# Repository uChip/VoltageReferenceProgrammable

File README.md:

Programmable Voltage Reference  
==============================

This repository contains the design files and write-up for a Programmable Voltage Reference.  The reference has a range of 1 mV to 4.095 volts in 1 mV steps.  The accuracy is plus or minus 100 uV for any set value.  The reference value is displayed on a 4 digit LED display and can be set manually using the rotary encoder or remotely over serial (FTDI port).

The software folder contains an Arduino sketch that is source code for the voltage reference firmware.

See the file PVR.pdf for a more detailed explanation of the project design. 

If there is sufficient interest I will build and calibrate a batch of these to sell.  If you would like one, please contact me. 

## Order PCBs  

You can order this PCB directly from OSH Park.  Click on the following link.  
  * Programmable Voltage Reference - https://oshpark.com/shared_projects/aFUNW4O5 

See the Bill of Materials (BOM) file in the repo Hardware folder for a parts list.  

## Status  
  * Rev-D PCB has been tested to be functional.  

## File Formats  

Hardware design files are in "CadSoft EAGLE PCB Design Software" .brd and .sch formats.  A free version of the software can be downloaded from www.cadsoftusa.com. 

The example code is in Arduino .ino format (text).  A free version of the Arduino software can be downloaded from www.arduino.cc.  

## Distribution License  

License:
<br /><span xmlns:dct="http://purl.org/dc/terms/" property="dct:title">Programmable Voltage Reference</span> by <a xmlns:cc="http://creativecommons.org/ns#" href="https://github.com/uChip/VoltageReferenceProgrammable" property="cc:attributionName" rel="cc:attributionURL">C.Schnarel</a> is licensed under a <a rel="license" href="http://creativecommons.org/licenses/by-sa/4.0/">Creative Commons Attribution-ShareAlike 4.0 International License</a>.

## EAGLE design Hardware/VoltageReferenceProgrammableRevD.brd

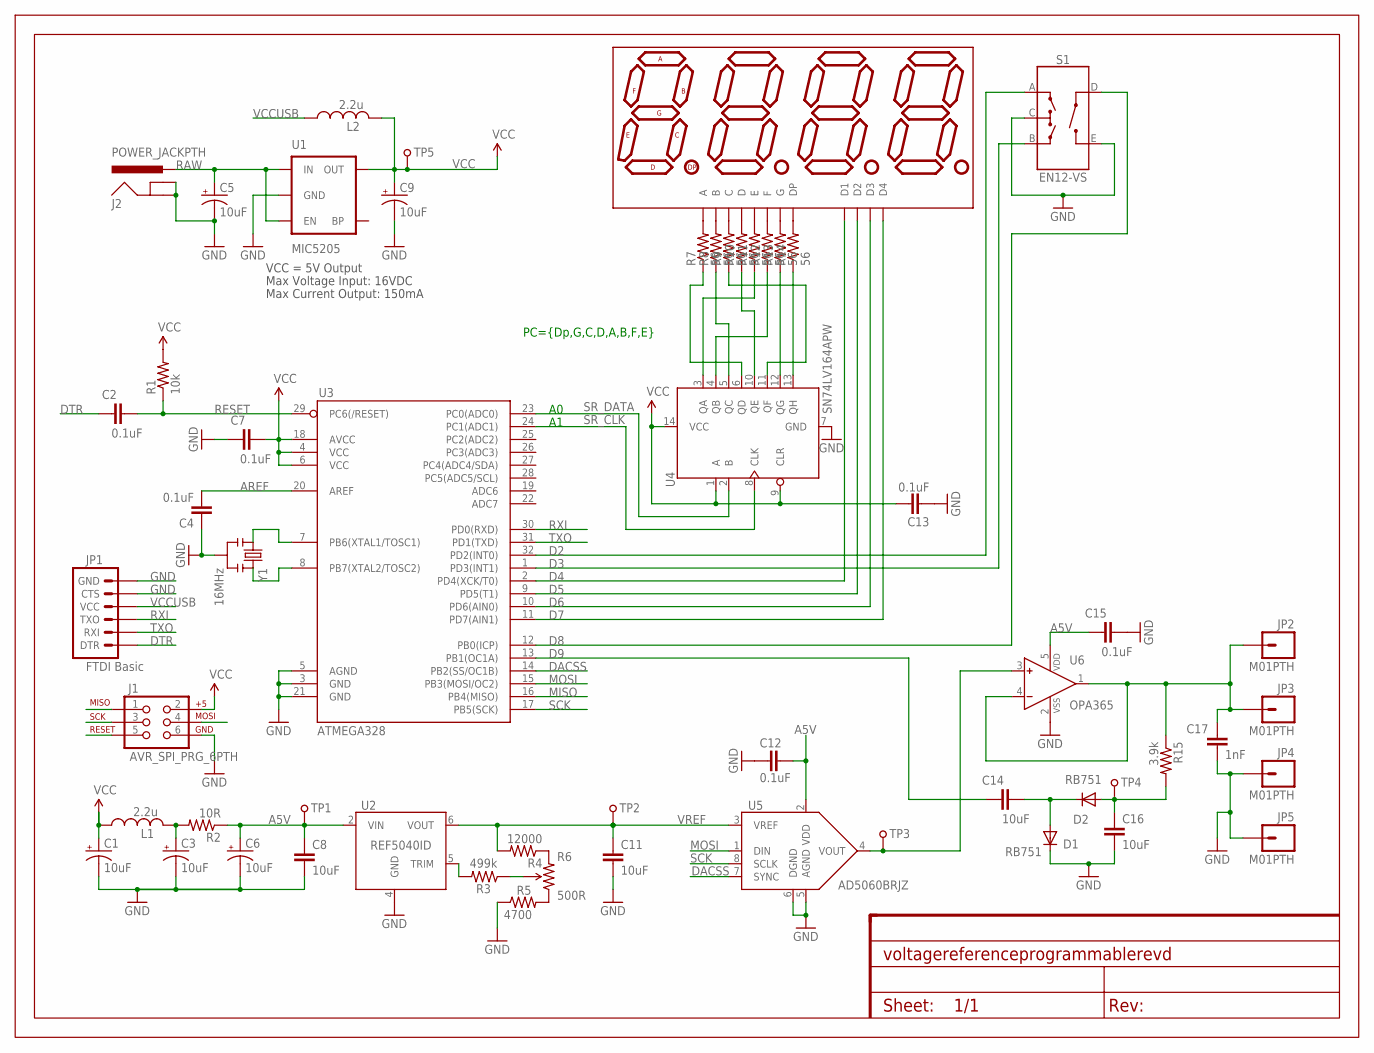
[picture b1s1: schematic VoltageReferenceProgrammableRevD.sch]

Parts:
C1, C3, C5, C6, C9: 10uF; 0805-POL
C2, C4, C7, C12, C13, C15: 0.1uF; 0805
C8, C11, C14, C16: 10uF; 0805
C17: 1nF; 0805
D1, D2: RB751; SOD-323
DISP1: hp; DIL12
FRAME1: FRAME_LTR_CU_MARK; FR-LTR-ON-PCB
J1: AVR_SPI_PRG_6PTH; 2X3
J2: POWER_JACKPTH; POWER_JACK_PTH
JP1: FTDI Basic; 1X06
JP2, JP3, JP4, JP5: M01PTH; 1X01
L1, L2: 2.2u; 0805
R1: 10k; 0805
R2: 10R; 0805
R3: 499k; 0805
R4: 12000; 0805
R5: 4700; 0805
R6: 500R; T93YB
R7, R8, R9, R10, R11, R12, R13, R14: 56; 0805
R15: 3.9k; 0805
S1: EN12-VS; ROTARY_ENCODER_SIDE
TP1, TP2, TP3, TP4, TP5: TEST_POINT; BBD-VIA
U1: MIC5205; SOT23-5
U2: REF5040ID; SOIC-8-MINUSPINS
U3: ATMEGA328; TQFP32-08
U4: SN74LV164APW; TSSOP-14(TI)
U5: AD5060BRJZ; SOT-23-8
U6: OPA365; SOT-23-5
Y1: 16MHz; RESONATOR-SMD

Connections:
A5V: C6.1 (+), C8.1, C12.1, C15.1, R2.1, TP1.P$1, U2.2 (VIN), U5.2 (VDD), U6.5 (VDD)
ADCIN: C16.1, D2.2 (A), R15.2, TP4.P$1
AREF: C4.2, U3.20 (AREF)
D2: S1.A, U3.32 (PD2(INT0))
D3: S1.B, U3.1 (PD3(INT1))
D4: DISP1.1 (D1), U3.2 (PD4(XCK/T0))
D5: DISP1.10 (D2), U3.9 (PD5(T1))
D6: DISP1.4 (D3), U3.10 (PD6(AIN0))
D7: DISP1.6 (D4), U3.11 (PD7(AIN1))
D8: S1.D, U3.12 (PB0(ICP))
D9: C14.1, U3.13 (PB1(OC1A))
DACSS: U3.14 (PB2(SS/OC1B)), U5.7 (SYNC)
DTR: C2.1, JP1.1 (DTR)
GND: C1.2 (-), C3.2 (-), C4.1, C5.2 (-), C6.2 (-), C7.1, C8.2, C9.2 (-), C11.2, C12.2, C13.2, C15.2, C16.2, C17.1, D1.1 (C), J1.6, J2.GND, J2.GNDBREAK, JP1.5 (CTS), JP1.6 (GND), JP4.1, JP5.1, R5.1, S1.C, S1.E, U1.2 (GND), U2.4 (GND), U3.3 (GND), U3.5 (AGND), U3.21 (GND), U4.7 (GND), U5.5 (AGND), U5.6 (DGND), U6.2 (VSS), Y1.2
MISO: J1.1, U3.16 (PB4(MISO))
MOSI: J1.4, U3.15 (PB3(MOSI/OC2)), U5.1 (DIN)
unnamed: U3.7 (PB6(XTAL1/TOSC1)), Y1.1
unnamed: U3.8 (PB7(XTAL2/TOSC2)), Y1.3
unnamed: DISP1.12 (A), R7.2
unnamed: DISP1.11 (B), R8.2
unnamed: DISP1.3 (C), R9.2
unnamed: DISP1.8 (D), R10.2
unnamed: R14.1, U4.13 (QH)
unnamed: DISP1.2 (E), R11.2
unnamed: DISP1.9 (F), R12.2
unnamed: DISP1.7 (G), R13.2
unnamed: DISP1.5 (DP), R14.2
unnamed: TP3.P$1, U5.4 (VOUT), U6.3 (IN+)
unnamed: C17.2, JP2.1, JP3.1, R15.1, U6.1 (OUT), U6.4 (IN-)
unnamed: R3.1, R6.2 (WIPER)
unnamed: R13.1, U4.12 (QG)
unnamed: C14.2, D1.2 (A), D2.1 (C)
unnamed: R3.2, U2.5 (TRIM)
unnamed: R5.2, R6.1 (CCW)
unnamed: R4.1, R6.3 (CW)
unnamed: R9.1, U4.11 (QF)
unnamed: R10.1, U4.10 (QE)
unnamed: R7.1, U4.6 (QD)
unnamed: R8.1, U4.5 (QC)
unnamed: R12.1, U4.4 (QB)
unnamed: R11.1, U4.3 (QA)
unnamed: C3.1 (+), L1.2, R2.2
RAW: C5.1 (+), J2.PWR, U1.1 (IN), U1.3 (EN)
RESET: C2.2, J1.5, R1.1, U3.29 (PC6(/RESET))
RXI: JP1.3 (TXO), U3.30 (PD0(RXD))
SCK: J1.3, U3.17 (PB5(SCK)), U5.8 (SCLK)
SR_CLK: U3.24 (PC1(ADC1)), U4.8 (CLK)
SR_DATA: U3.23 (PC0(ADC0)), U4.2 (B)
TXO: JP1.2 (RXI), U3.31 (PD1(TXD))
VCC: C1.1 (+), C7.2, C9.1 (+), C13.1, J1.2, L1.1, L2.2, R1.2, TP5.P$1, U1.5 (OUT), U3.4 (VCC), U3.6 (VCC), U3.18 (AVCC), U4.1 (A), U4.9 (CLR), U4.14 (VCC)
VCCUSB: JP1.4 (VCC), L2.1
VREF: C11.1, R4.2, TP2.P$1, U2.6 (VOUT), U5.3 (VREF)

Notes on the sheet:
Max Voltage Input: 16VDC
Max Current Output: 150mA
VCC = 5V Output
PC={Dp,G,C,D,A,B,F,E}

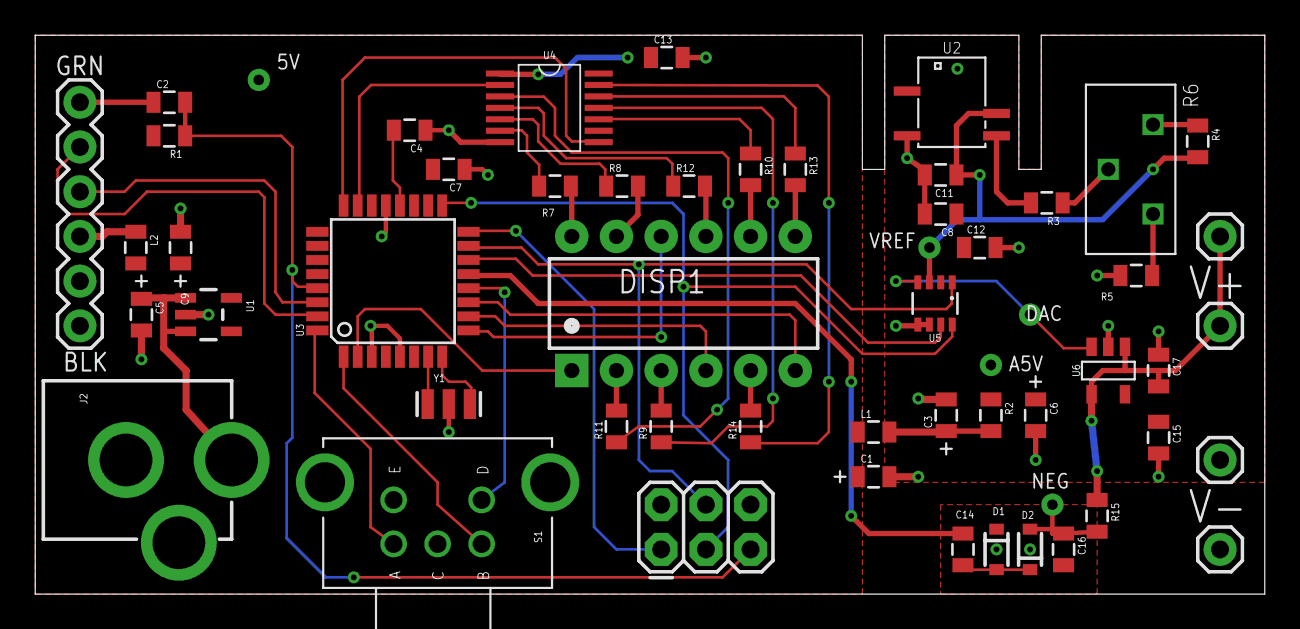
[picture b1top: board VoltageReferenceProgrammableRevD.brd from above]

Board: 2 copper layers, 69.8 x 31.8 mm, 57 parts (0 on the bottom side), 52 nets.

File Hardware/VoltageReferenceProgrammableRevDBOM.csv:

"Qty;""Value"";""Device"";""Package"";""Parts"";""Description"";""CNAME"";""CREVISION"";""DATECODE"";""DESIGNER"";",,,,,,,
"6;""0.1uF"";""CAP0805"";""0805"";""C2", C4, C7, C12, C13," C15"";""Capacitor"";"""";"""";"""";"""";",,
"1;""10R"";""RESISTOR0805-RES"";""0805"";""R2"";""Resistor"";"""";"""";"""";"""";",,,,,,,
"1;""10k"";""RESISTOR0805-RES"";""0805"";""R1"";""Resistor"";"""";"""";"""";"""";",,,,,,,
"4;""10uF"";""CAP0805"";""0805"";""C8", C11, C14," C16"";""Capacitor"";"""";"""";"""";"""";",,,,
"5;""10uF"";""CAP_POL0805"";""0805-POL"";""C1", C3, C5, C6," C9"";"""";"""";"""";"""";"""";",,,
"1;""12000"";""RESISTOR0805-RES"";""0805"";""R4"";""Resistor"";"""";"""";"""";"""";",,,,,,,
"1;""16MHz"";""RESONATORSMD"";""RESONATOR-SMD"";""Y1"";""Resonator"";"""";"""";"""";"""";",,,,,,,
"1;""1nF"";""CAP0805"";""0805"";""C17"";""Capacitor"";"""";"""";"""";"""";",,,,,,,
"2;""2.2u"";""INDUCTOR"";""0805"";""L1"," L2"";""Inductor", SMT chip," 0805 pkg"";"""";"""";"""";"""";",,,,
"1;""3.9k"";""RESISTOR0805-RES"";""0805"";""R15"";""Resistor"";"""";"""";"""";"""";",,,,,,,
"1;""4700"";""RESISTOR0805-RES"";""0805"";""R5"";""Resistor"";"""";"""";"""";"""";",,,,,,,
"1;""499k"";""RESISTOR0805-RES"";""0805"";""R3"";""Resistor"";"""";"""";"""";"""";",,,,,,,
"1;""500R"";""TRIMPOT"";""T93YB"";""R6"";""Various small potentiometers for ""set-and-forget"" applications"";"""";"""";"""";"""";",,,,,,,
"8;""56"";""RESISTOR0805-RES"";""0805"";""R7", R8, R9, R10, R11, R12, R13," R14"";""Resistor"";"""";"""";"""";"""";"
"1;""AD5060BRJZ"";""AD5060BRJZ"";""SOT-23-8"";""U5"";"""";"""";"""";"""";"""";",,,,,,,
"1;""ATMEGA328"";""ATMEGA168"";""TQFP32-08"";""U3"";"""";"""";"""";"""";"""";",,,,,,,
"1;""AVR_SPI_PRG_6PTH"";""AVR_SPI_PRG_6PTH"";""2X3"";""J1"";""AVR ISP 6 Pin"";"""";"""";"""";"""";",,,,,,,
"1;""EN12-VS"";""EN12-VS"";""ROTARY_ENCODER_SIDE"";""S1"";""Rotary Encoder w push switch", quadrature," 12 pulse/rev.  BI Technologies. Digi-key#987-1198-ND"";"""";"""";"""";"""";",,,,,
"1;""FRAME_LTR_CU_MARK"";""FRAME_LTR_CU_MARK"";""FR-LTR-ON-PCB"";""FRAME1"";""This frame is sized for an 8.5x11"" page with a 0.25"" margin.  It also places a name"," datecode and revision mark in the bottom copper layer of the PCB."";""C.Schnarel"";""ProgVRef Rev-D"";""24AUG2014"";""C.Schnarel"";",,,,,,
"1;""FTDI Basic"";""ARDUINO_SERIAL_PROGRAMPTH"";""1X06"";""JP1"";"""";"""";"""";"""";"""";",,,,,,,
"4;""M01PTH"";""M01PTH"";""1X01"";""JP2", JP3, JP4," JP5"";""Header 1"";"""";"""";"""";"""";",,,,
"1;""MIC5205"";""V_REG_LDOSMD"";""SOT23-5"";""U1"";""Voltage Regulator LDO"";"""";"""";"""";"""";",,,,,,,
"1;""OPA365"";""OPA365"";""SOT-23-5"";""U6"";""OpAmp", 50MHz, R-to-R, single-supply, CMOS, TI," Digi-Key#296-20645-1-ND"";"""";"""";"""";"""";",
"1;""POWER_JACKPTH"";""POWER_JACKPTH"";""POWER_JACK_PTH"";""J2"";""Power Jack"";"""";"""";"""";"""";",,,,,,,
"2;""RB751"";""DIODESOD"";""SOD-323"";""D1"," D2"";""Diode"";"""";"""";"""";"""";",,,,,,
"1;""REF5040ID"";""REF5040ID"";""SOIC-8-MINUSPINS"";""U2"";"""";"""";"""";"""";"""";",,,,,,,
"1;""SN74LV164APW"";""SN74LV164APW"";""TSSOP-14(TI)"";""U4"";""8-BIT SERIAL-IN PARALLEL-OUT SHIFT REGISTER with clear"";"""";"""";"""";"""";",,,,,,,
"5;""TEST_POINT"";""TEST_POINT"";""BBD-VIA"";""TP1", TP2, TP3, TP4," TP5"";""Test Point"";"""";"""";"""";"""";",,,
"1;""hp"";""7-SEGMENT-4DIGIT-COUNTER-HP-BUBBLE"";""DIL12"";""DISP1"";"""";"""";"""";"""";"""";",,,,,,,

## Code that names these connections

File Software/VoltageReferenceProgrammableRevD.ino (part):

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#define MAX_OFFSETS 10

// Pins to drive Segment Shift Register
#define SR_DATA A0
#define SR_CLK A1

// Display digit pins
#define DIGIT_1 4
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#define BUTTON 8

// DAC Slave Select
#define DACSS 10

// This sets the delay time for frame rate
// The value is repeated for each of the digits on the display so 
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// send refVal to DAC after adding correction factor
#define CORRECTED true
// send raw refVal numbers to the DAC w/o correcting
#define RAW false

// Character generator for 7-segment displays
static uint8_t	chargen[] = {
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  button.update();
  if(button.read() == LOW) {mode = RAW;} else {mode = CORRECTED;}

  pinMode(SR_DATA, OUTPUT);
  pinMode(SR_CLK, OUTPUT);
  
  // set up the digit control pins
  pinMode(DIGIT_1, OUTPUT);
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  // set up the select control pin for the DAC
  // DAC select is active low, data is shifted in MSB first
  // on the falling edge of the clock
  pinMode(DACSS, OUTPUT);
  digitalWrite(DACSS, HIGH);
  SPI.begin();
  SPI.setDataMode(SPI_MODE1);  // set to falling edge clock
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
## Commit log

2014-12-25 :boom::camel: Added .gitattributes & .gitignore files
2014-12-25 Starting README.md
2014-12-28 Added content to README
2014-12-28 Added license reference
2014-12-28 Added selling paragraph
2014-12-28 README edits
2014-12-28 Syncing URLs
2014-12-28 Generated pdf from latest changes
2014-12-28 Saving PDFs of schematic and board
2014-12-30 Edits on write-up
2015-04-12 Updated software
    Added comments to doc sources of libraries.
    Updated Bounce lbr to Bounce2 and made associated changes to code.
2015-04-12 Corrected error on schematic & BOM
    AD5040 was replaced with AD5060.
2015-04-14 Updated BOM to note potential part subst
    to make assembly easier for some folks.

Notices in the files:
parts and their libraries:
SparkFun-Displays: Licensing: Creative Commons ShareAlike 4.0 International - https://creativecommons.org/licenses/by-sa/4.0
SparkFun-Capacitors: Licensing: CC v3.0 Share-Alike You are welcome to use this library for commercial purposes.
